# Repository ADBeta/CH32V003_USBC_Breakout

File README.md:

# CH32V003 USB C Breakout

## Project Description
A Breakout Board for the QFN Variant of the CH32V003, with pins broken out for
I2C, SPI, UART, USB, and with a USB-C Connector, and an NRST Button.  

This Board has been designed with generic and minimal parts, to make the
production and assembly of these boards easy and cheap for novices, looking to
get into the hobby and/or use the `CH32V003` Chips

NOTE: If using the USB Pins for other purposes, please keep in mind that USB_DM
and USB_PU are connected togehter with a 1.5K resistor. Remove this if needed

## Gallery

## Parts List
`J2    Generic 16 Pin USB C Connector`  
`J1     3 x 2.54mm (0.1") Pin Header`  
`J3    12 x 2.54mm (0.1") Pin Header`  
`J4    12 x 2.54mm (0.1") Pin Header`  

`R1    0805 1.5K Resistor`  
`R2    0805 5.1K Resistor (Can leave unpopulated, or use 5K - 22K instead)`  
`R3    0805 5.1K Resistor (Can leave unpopulated, or use 5K - 22K instead)`  

`C1    0805 100nF Capacitor`  
`C2    0805 100nF Capacitor`  
`C3    0805 10uF  Capacitor (Can leave unpopulated, or use 100nF instead)`  

`SW1   Generic 6mm x 3mm Tactile Button`  

`U1    QFN20 0.4mm Pitch CH32V003`  
`U2    AMS1117 3.3c Voltage Regulator`  

## Pinout
**USB**
   * `Pullup  PD2`
   * `D-      PD3`
   * `D+      PD4`

**SPI**
   * `SCLK    PC5`
   * `MOSI    PC6`
   * `MISO    PC7`

**I2C**
   * `SDA     PC1`
   * `SCL     PC2`

**UART**
   * `TX      PD5`
   * `RX      PD6`

## Dimensions
The PCB is 22mm x 40mm, with 4 x 2.6mm holes in a rectangle pattern; 18mm x 36mm.  

----
Copyright (c) ADBeta 2024    Last Modified: 29 May 2024

This program is free software; you can redistribute it and/or modify it under
the terms of the GNU General Public License as published by the Free Software
Foundation; either version 2 of the License, 
or (at your option) any later version.

This program is distributed in the hope that it will be useful, but 
WITHOUT ANY WARRANTY; without even the implied warranty of MERCHANTABILITY or
FITNESS FOR A PARTICULAR PURPOSE.  
See the GNU General Public License for more details.

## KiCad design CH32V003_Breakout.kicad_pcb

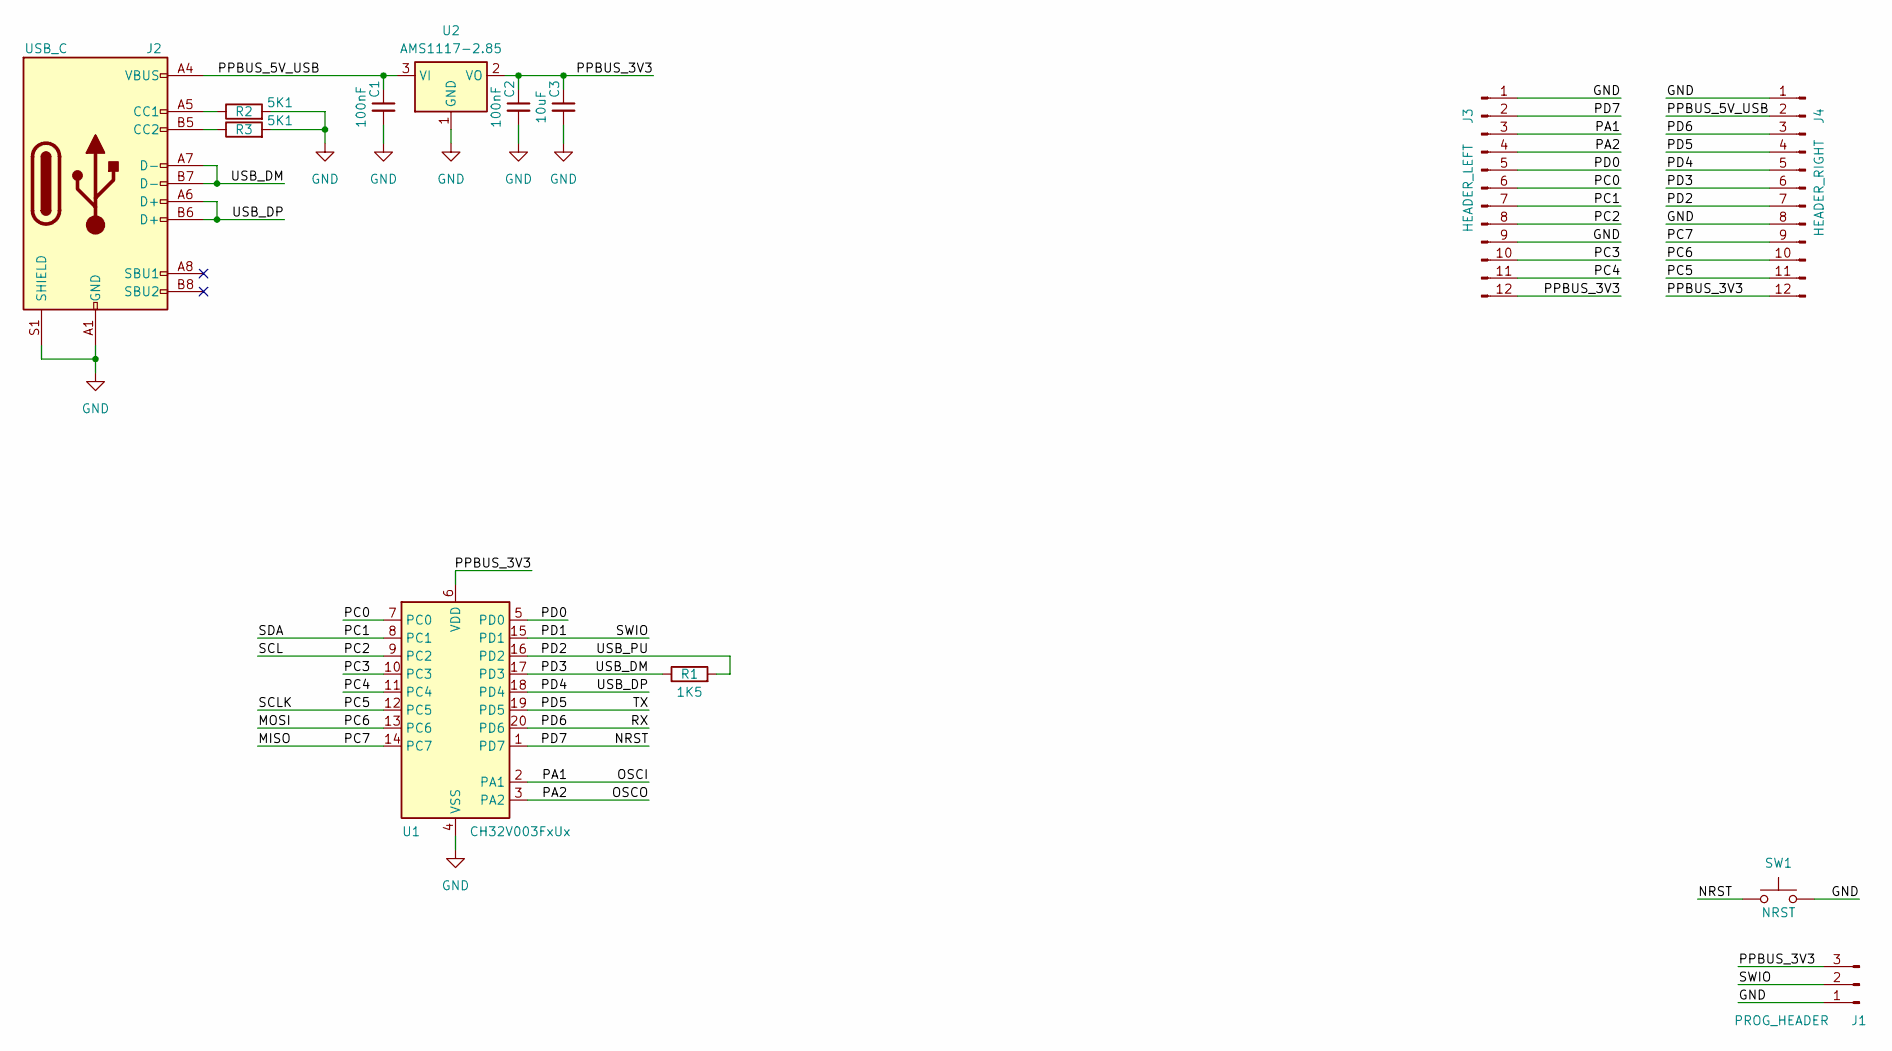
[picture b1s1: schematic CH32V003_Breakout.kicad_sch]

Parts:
C1, C2: 100nF; C_0805_2012Metric
C3: 10uF; C_0805_2012Metric
J1: PROG_HEADER; PinSocket_1x03_P2.54mm_Vertical
J2: USB_C; USB_C_Receptacle_G-Switch_GT-USB-7010ASV
J3: HEADER_LEFT; PinSocket_1x12_P2.54mm_Vertical
J4: HEADER_RIGHT; PinSocket_1x12_P2.54mm_Vertical
R1: 1K5; R_0805_2012Metric
R2, R3: 5K1; R_0805_2012Metric
SW1: NRST; SW_SPST_TL3342
U1: CH32V003FxUx; QFN-20-1EP_3x3mm_P0.4mm_EP1.65x1.65mm
U2: AMS1117-2.85; SOT-223-3_TabPin2

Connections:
/MISO: J4.9, U1.14 (PC7)
/MOSI: J4.10, U1.13 (PC6)
/NRST: J3.2, SW1.1, U1.1 (PD7)
/OSCI: J3.3, U1.2 (PA1)
/OSCO: J3.4, U1.3 (PA2)
/PC0: J3.6, U1.7 (PC0)
/PC1: J3.7, U1.8 (PC1)
/PC2: J3.8, U1.9 (PC2)
/PC3: J3.10, U1.10 (PC3)
/PC4: J3.11, U1.11 (PC4)
/PC5: J4.11, U1.12 (PC5)
/PD0: J3.5, U1.5 (PD0)
/PD1: J1.2, U1.15 (PD1)
/PD2: J4.7, R1.2, U1.16 (PD2)
/PD3: J2.A7 (D-), J2.B7 (D-), J4.6, R1.1, U1.17 (PD3)
/PD4: J2.A6 (D+), J2.B6 (D+), J4.5, U1.18 (PD4)
/PD5: J4.4, U1.19 (PD5)
/PD6: J4.3, U1.20 (PD6)
/PPBUS_3V3: C2.1, C3.1, J1.3, J3.12, J4.12, U1.6 (VDD), U2.2 (VO)
/PPBUS_5V_USB: C1.1, J2.A4 (VBUS), J2.A9 (VBUS), J2.B4 (VBUS), J2.B9 (VBUS), J4.2, U2.3 (VI)
GND: C1.2, C2.2, C3.2, J1.1, J2.A1 (GND), J2.A12 (GND), J2.B1 (GND), J2.B12 (GND), J2.S1 (SHIELD), J3.1, J3.9, J4.1, J4.8, R2.2, R3.2, SW1.2, U1.4 (VSS), U1.21 (VSS), U2.1 (GND)
unnamed: J2.A5 (CC1), R2.1
unnamed: J2.B5 (CC2), R3.1

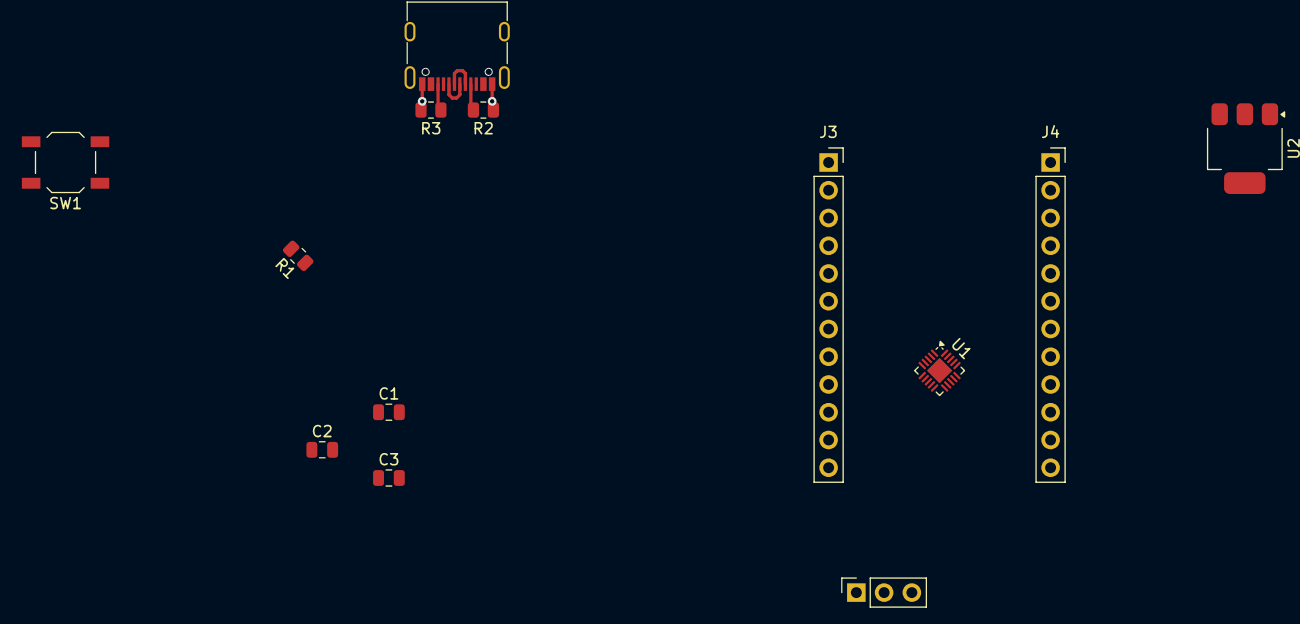
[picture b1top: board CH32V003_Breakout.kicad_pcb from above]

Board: 2 copper layers, 13 parts (0 on the bottom side), 23 nets.

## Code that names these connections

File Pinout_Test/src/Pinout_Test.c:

/******************************************************************************
* A very simple program to test all of the Pins on the breakout board to 
* ensure all pins are soldered correctly.
*
* Attach 1K resitors and LEDs to each of the pins listed in the program.
*
* ADBeta (c)   2024
******************************************************************************/
#include "lib_GPIOCTRL.h"
#include "ch32v003fun.h"
#include <stdio.h>

const gpio_pin_t port_a[] = {GPIO_PA1, GPIO_PA2};
const gpio_pin_t port_c[] = {GPIO_PC0, GPIO_PC1, GPIO_PC2, GPIO_PC3, GPIO_PC4, GPIO_PC5, GPIO_PC6, GPIO_PC7};
// PD1 is SWIO and PD7 is NRST
const gpio_pin_t port_d[] = {GPIO_PD0, GPIO_PD2, GPIO_PD3, GPIO_PD4, GPIO_PD5, GPIO_PD6};


int main()
{
	SystemInit();



	// Setup all the applicable pins
	for(uint8_t pai = 0; pai < 2; pai++) gpio_digital_write(port_a[pai], GPIO_HIGH);
	for(uint8_t pci = 0; pci < 8; pci++) gpio_digital_write(port_c[pci], GPIO_HIGH);
	for(uint8_t pdi = 0; pdi < 6; pdi++) gpio_digital_write(port_d[pdi], GPIO_HIGH);


	while(1)
	{
		/* PORT A */
		for(uint8_t pai = 0; pai < 2; pai++)
		{
			gpio_digital_write(port_a[pai], GPIO_HIGH);
			gpio_set_mode(port_a[pai], OUTPUT_10MHZ_PP);
			Delay_Ms(250);
			gpio_set_mode(port_a[pai], INPUT_FLOATING);
		}


		/* PORT C */
		for(uint8_t pci = 0; pci < 8; pci++)
		{
			gpio_digital_write(port_c[pci], GPIO_HIGH);
			gpio_set_mode(port_c[pci], OUTPUT_10MHZ_PP);
			Delay_Ms(250);
			gpio_set_mode(port_c[pci], INPUT_FLOATING);
		}


		/* PORT D */
		for(uint8_t pdi = 0; pdi < 6; pdi++)
		{
			gpio_digital_write(port_d[pdi], GPIO_HIGH);
			gpio_set_mode(port_d[pdi], OUTPUT_10MHZ_PP);
			Delay_Ms(250);
			gpio_set_mode(port_d[pdi], INPUT_FLOATING);
		}
	}
}

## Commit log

2024-05-28 fixed readme pinout
2024-05-28 Started PCB Layout
2024-05-29 V1.0 Board Release
2024-05-29 Fixed Readme
2024-06-19 Added pinout test
